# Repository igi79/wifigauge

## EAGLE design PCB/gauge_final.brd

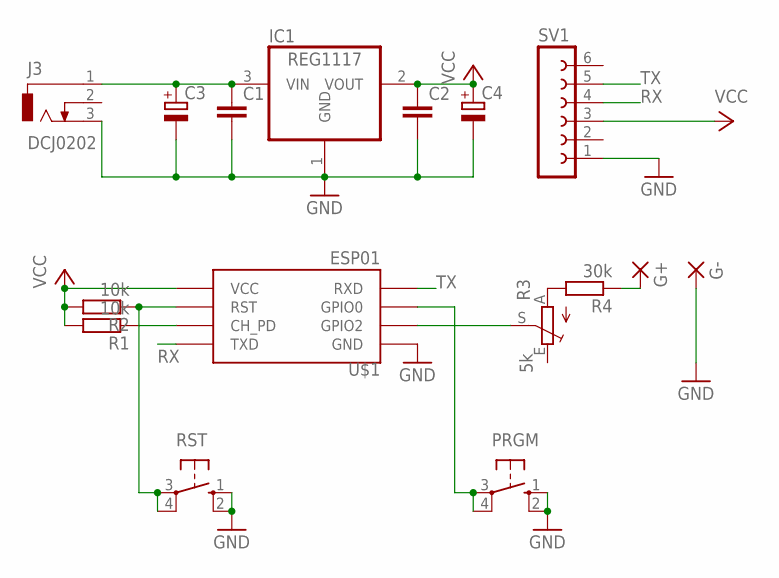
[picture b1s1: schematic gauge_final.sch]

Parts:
C1, C2: C-EUC0805; C0805
C3, C4: CPOL-EUSMCE; SMC_E
G+: 3,81/1,4
G-: 3,81/1,4
IC1: REG1117; SOT223
J3: DCJ0202
PRGM: 10-XX; B3F-10XX
R1, R2: 10k; R0805
R3: 5k; SP19L
R4: 30k; R0805
RST: 10-XX; B3F-10XX
SV1: FE06-1; FE06
U$1: ESP01

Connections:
GND: C1.2, C2.2, C3.-, C4.-, G-.1, IC1.1 (GND), J3.3, PRGM.1 (S), PRGM.2 (S1), RST.1 (S), RST.2 (S1), SV1.1, U$1.GND
unnamed: R2.1, RST.3, RST.4 (P1), U$1.RST
unnamed: R1.1, U$1.CH_PD
unnamed: G+.1, R4.1
unnamed: PRGM.3, PRGM.4 (P1), U$1.GPIO0
unnamed: R3.S, U$1.GPIO2
unnamed: C1.1, C3.+, IC1.3 (VIN), J3.1
unnamed: R3.A, R4.2
RX: SV1.4, U$1.TX (TXD)
TX: SV1.5, U$1.RX (RXD)
VCC: C2.1, C4.+, IC1.2 (VOUT), R1.2, R2.2, SV1.3, U$1.VCC

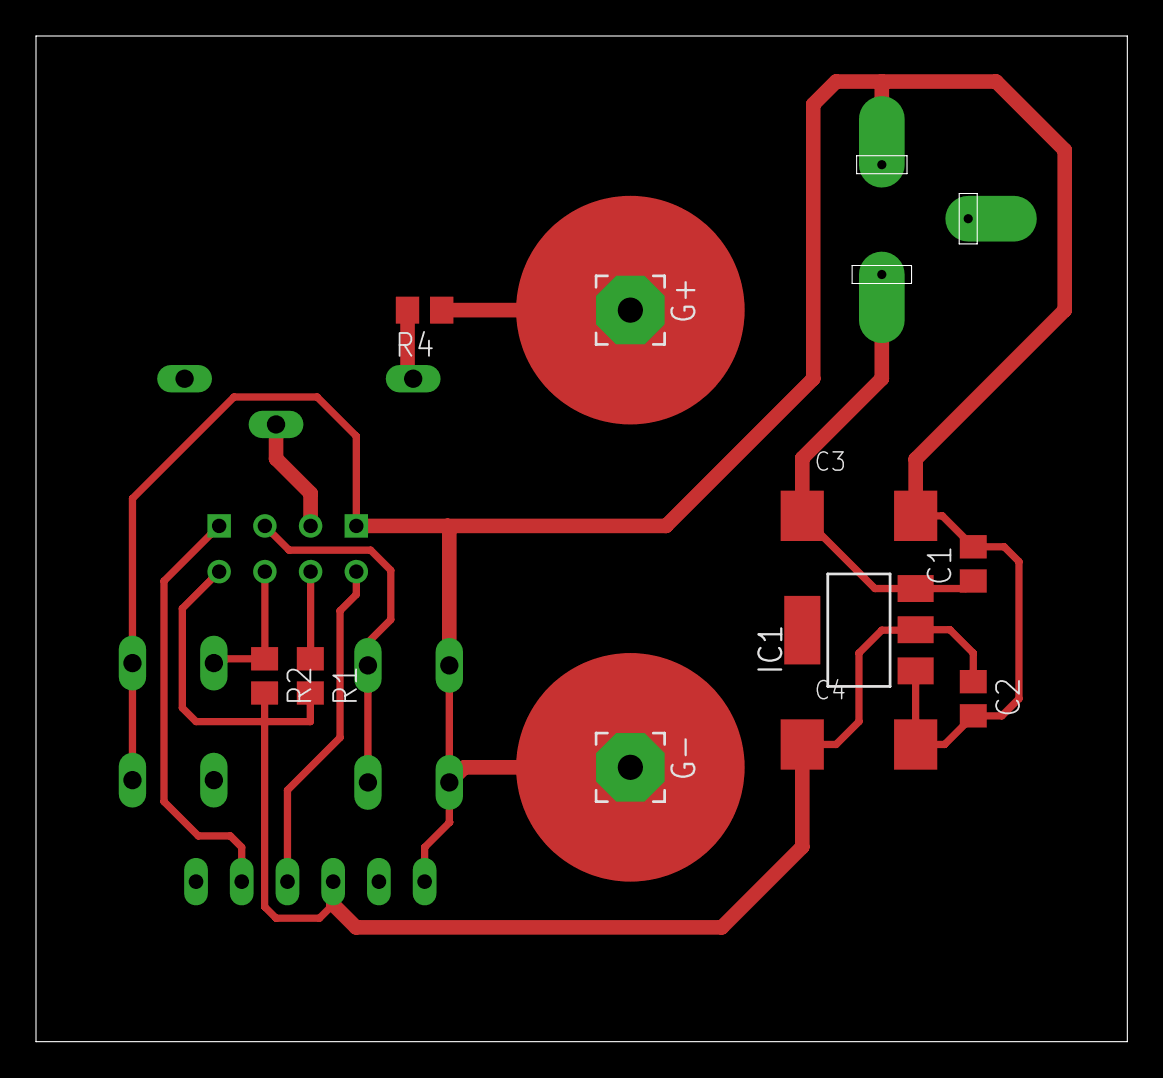
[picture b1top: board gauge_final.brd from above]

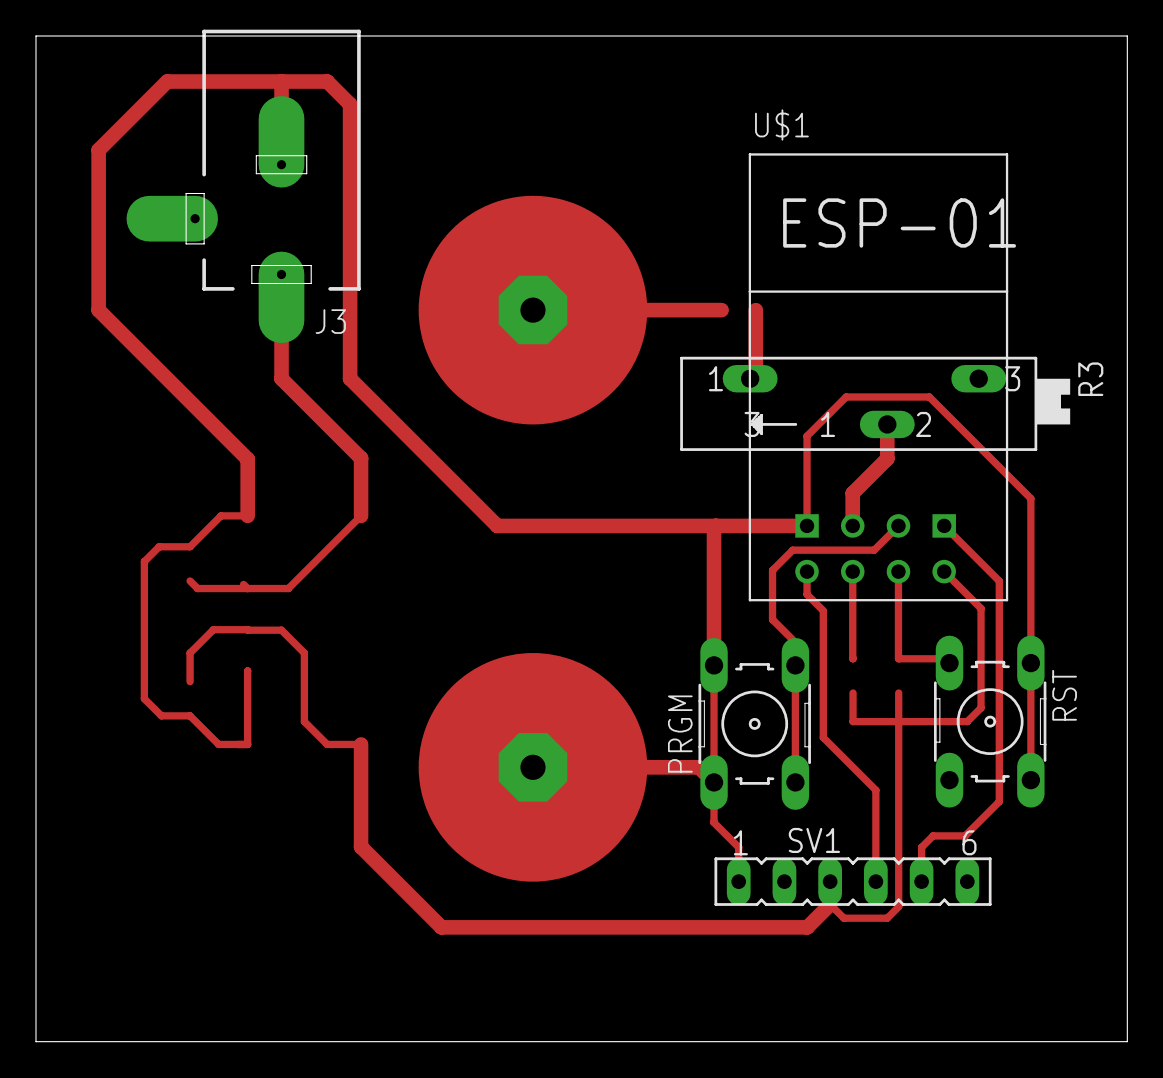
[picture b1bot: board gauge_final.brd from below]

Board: 2 copper layers, 60.6 x 55.9 mm, 16 parts (6 on the bottom side), 11 nets.

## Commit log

2021-04-05 init
